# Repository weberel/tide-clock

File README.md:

# Tide Clock

A battery-powered e-paper display showing tide times. Configurable for any coastal location. This device does not need an internet or bluetooth connection as all data is calculated on the device itself from a given time and location. Thanks to the display type and slow refreshrate with long sleep cycles this device can operate on two AA-batteries for at least 3 years.

## Features

- **Tide prediction** - Next high/low tide times using a 31-constituent harmonic model
- **Moon phase** - Current phase with upcoming full/new moon dates
- **Sunrise/Sunset** - Daily times with 24-hour daylight visualization bar
- **Special messages** - Solstices, equinoxes, eclipses, meteor showers, holidays
- **Offline operation** - Pure mathematical models, no internet required
- **Multi-year battery life** - 15-minute wake cycles with deep sleep between updates

## Hardware

- **MCU**: STM32F411RET6 (ARM Cortex-M4)
- **Display**: 2.9" e-paper (296x128, SSD1680 controller)
- **RTC**: DS3231MZ+ with alarm wake
- **Power**: AA batteries with TPS61099 boost converter

## Project Structure

```
tidal-clock/
├── firmware/          # STM32 firmware (Rev A & B)
├── simulator/         # SDL2 simulator for testing
├── scripts/           # Location config generation
│   └── harmonic_fitting/  # Tide model fitting
├── kicad/             # PCB designs
└── manual/            # User manual
```

Each folder has its own README with detailed instructions.

## Quick Start

### Simulator

```bash
cd simulator
sudo apt install libsdl2-dev
git clone https://github.com/olikraus/u8g2.git
make && ./tide_sim
```

### Firmware

```bash
cd firmware/revA  # or revB
cd lib && git clone https://github.com/olikraus/u8g2.git && cd ..
pio run --target upload
```

## Customizing Location

Configure for any coastal location. See [scripts/README.md](scripts/README.md) for details.

**US locations** (using NOAA API):
```bash
cd scripts
python3 generate_location.py --noaa 9414290 --name "San Francisco" --tz US_PACIFIC
```

**Other locations** (fit your own model):
```bash
python3 generate_location.py --json harmonic_fitting/model.json --name "Location" --tz UK
```

## License

MIT

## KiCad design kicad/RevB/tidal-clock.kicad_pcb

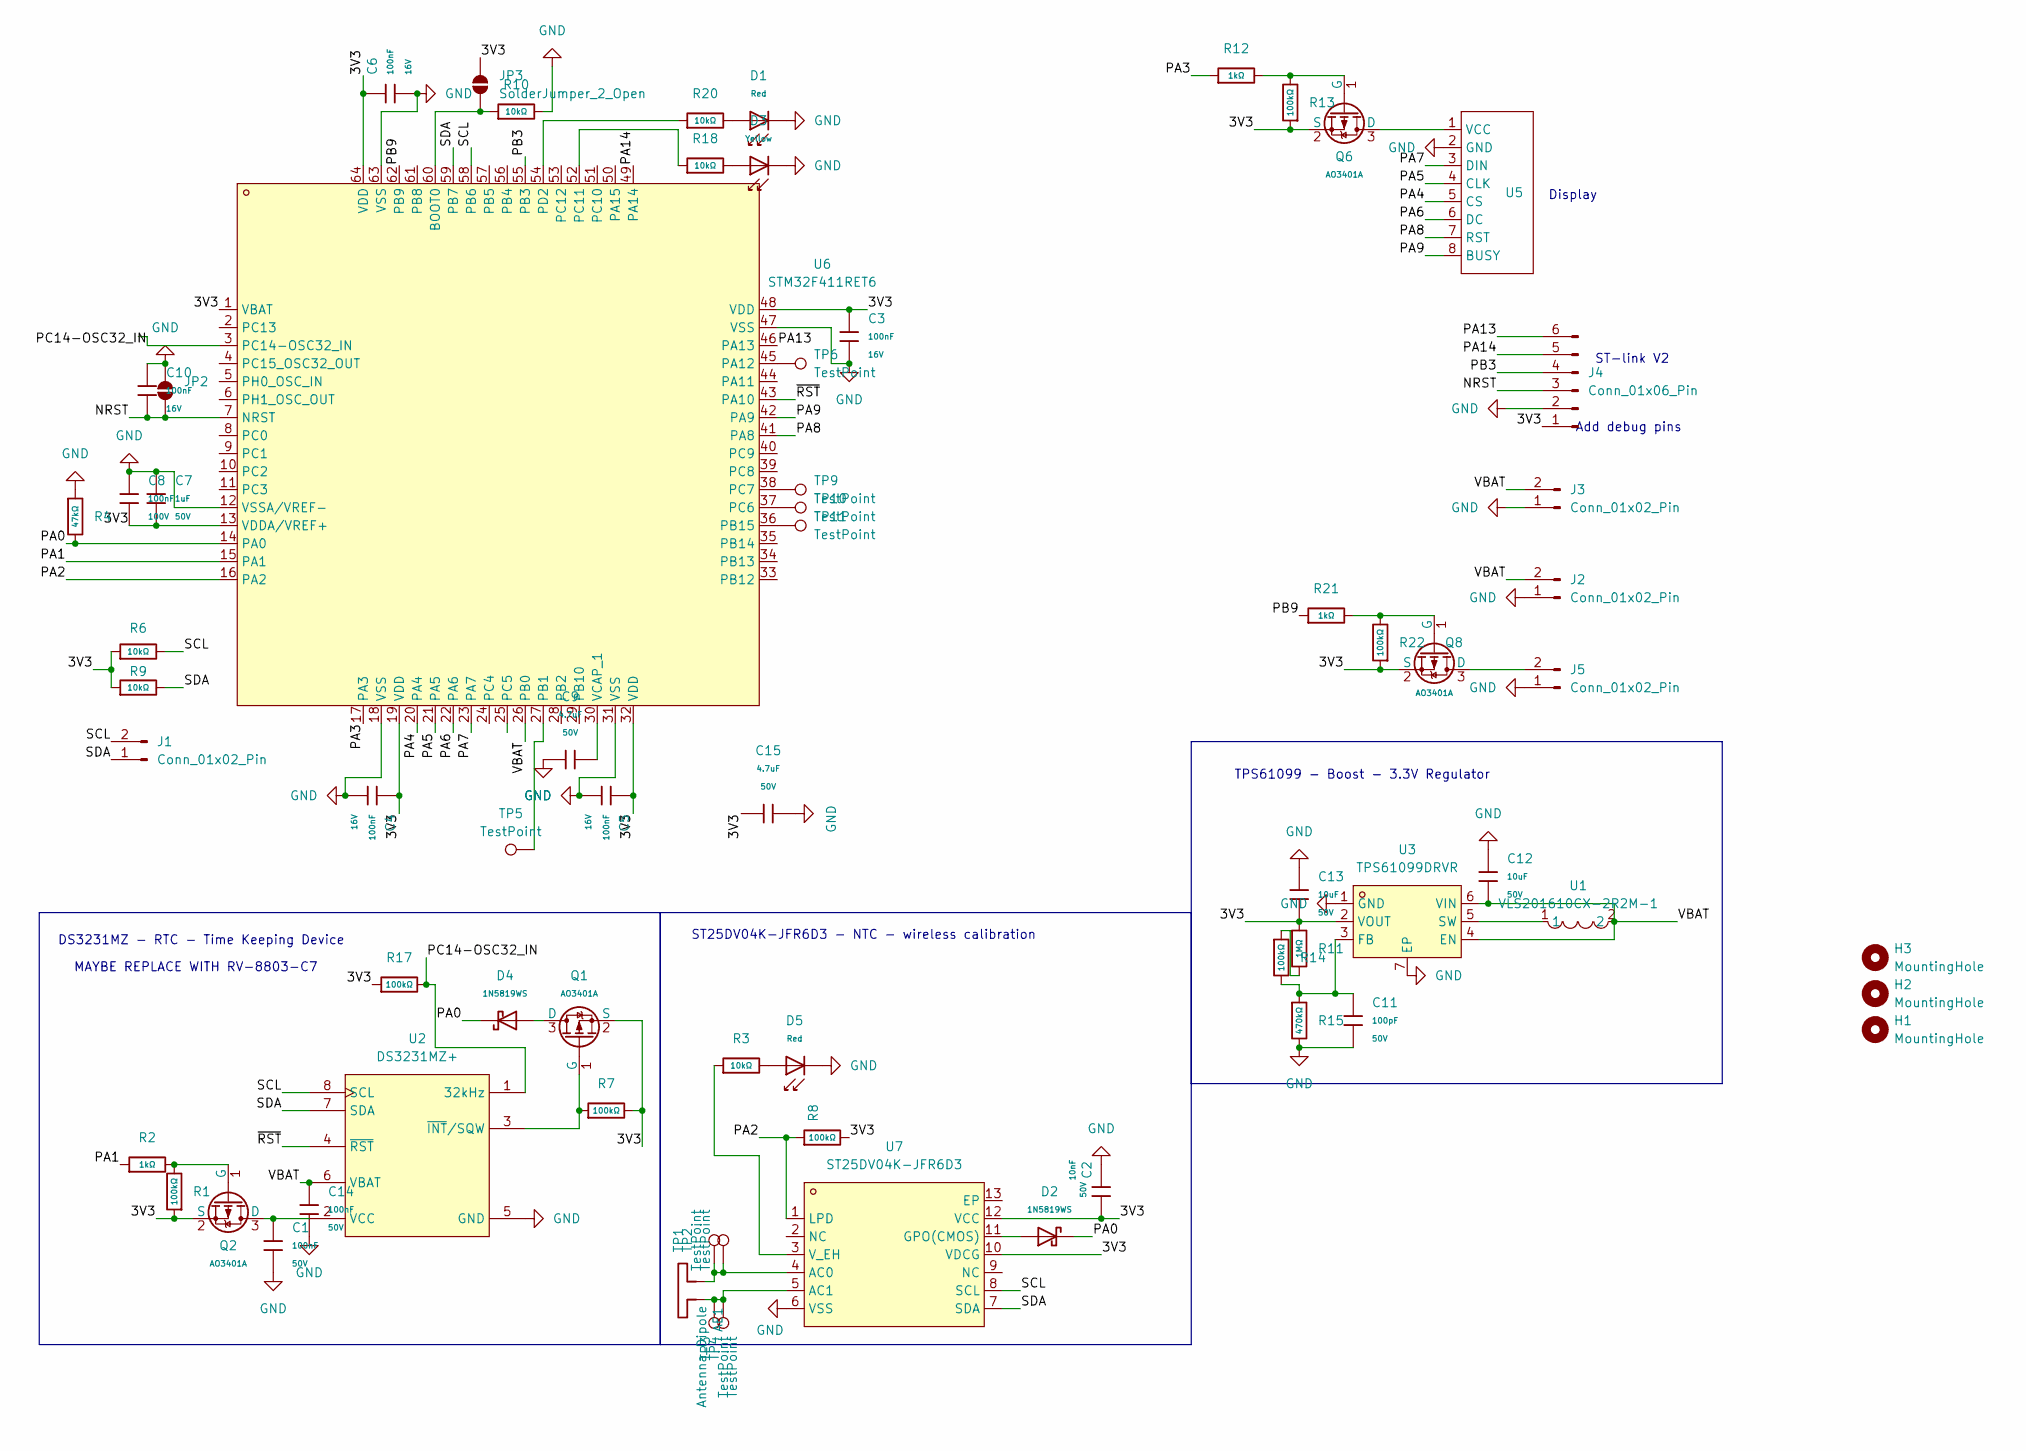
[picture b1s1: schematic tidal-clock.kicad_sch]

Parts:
AE1: Antenna_Dipole; NFC_COIL
C1, C14: 100nF; C_0603; Voltage Rated 50V; Tolerance ±10%; Part CC0603KRX7R9BB104; LCSC C14663
C2: 10nF; C_0402; Voltage Rated 50V; Tolerance ±10%; Part CL05B103KB5NNNC; LCSC C15195
C3, C4, C5, C6, C10: 100nF; C_0402; Voltage Rated 16V; Tolerance ±10%; Part CL05B104KO5NNNC; LCSC C1525
C7: 1uF; C_0805; Voltage Rated 50V; Tolerance ±10%; Part CL21B105KBFNNNE; LCSC C28323
C8: 100nF; C_0805; Voltage Rated 100V; Tolerance ±10%; Part CL21B104KCFNNNE; LCSC C28233
C9, C15: 4.7uF; C_1206; Voltage Rated 50V; Tolerance ±10%; Part 1206B475K500NT; LCSC C29823
C11: 100pF; C_0402; Voltage Rated 50V; Tolerance ±5%; Part 0402CG101J500NT; LCSC C1546
C12, C13: 10uF; C_1206; Voltage Rated 50V; Tolerance ±10%; Part CL31A106KBHNNNE; LCSC C13585
D1, D5: Red; D_0603; Part KT-0603R; LCSC C2286
D2, D4: 1N5819WS; D_SOD-323; Forward Voltage (Vf@If) 600mV@1A; Reverse Voltage (Vr) 40V; Part 1N5819WS; LCSC C191023
D3: Yellow; D_0603; Forward Voltage (VF) 1.6V~2.6V; Part NCD0603Y2; LCSC C89811
H1, H2, H3: MountingHole; MountingHole_2.2mm_M2_ISO14580
J1, J2, J3, J5: Conn_01x02_Pin; PinHeader_1x02_P2.54mm_Vertical
J4: Conn_01x06_Pin; PinSocket_1x06_P2.54mm_Vertical
JP2, JP3: SolderJumper_2_Open; SolderJumper-2_P1.3mm_Open_RoundedPad1.0x1.5mm
Q1, Q2, Q6, Q8: AO3401A; Q_SOT-23; Part AO3401A; LCSC C15127
R1, R7, R8, R13, R14, R17, R22: 100kΩ; R_0603; Overload Voltage (Max) 75V; Tolerance ±1%; Part 0603WAF1003T5E; LCSC C25803
R2, R12, R21: 1kΩ; R_0603; Overload Voltage (Max) 75V; Tolerance ±1%; Part 0603WAF1001T5E; LCSC C21190
R3, R18, R20: 10kΩ; R_0402; Overload Voltage (Max) 50V; Tolerance ±1%; Part 0402WGF1002TCE; LCSC C25744
R4: 47kΩ; R_0603; Overload Voltage (Max) 75V; Tolerance ±1%; Part 0603WAF4702T5E; LCSC C25819
R6, R9, R10: 10kΩ; R_0603; Overload Voltage (Max) 75V; Tolerance ±1%; Part 0603WAF1002T5E; LCSC C25804
R11: 1MΩ; R_0603; Overload Voltage (Max) 75V; Tolerance ±1%; Part 0603WAF1004T5E; LCSC C22935
R15: 470kΩ; R_0603; Overload Voltage (Max) 75V; Tolerance ±1%; Part 0603WAF4703T5E; LCSC C23178
TP1, TP2, TP3, TP4: TestPoint; TestPoint_Pad_1.0x1.0mm
TP5, TP6, TP9, TP10, TP11: TestPoint; TestPoint_Pad_D1.5mm
U1: VLS201610CX-2R2M-1; IND-SMD_L2.0-W1.6; LCSC Part C2041554
U2: DS3231MZ+; SOIC-8_L4.9-W3.9-P1.27-LS6.0-BL; LCSC Part C107410
U3: TPS61099DRVR; WSON-6_L2.0-W2.0-P0.65-TL-EP; LCSC Part C2842395
U5: PinHeader_1x08_P2.54mm_Vertical
U6: STM32F411RET6; LQFP-64_L10.0-W10.0-P0.50-LS12.0-BL; LCSC Part C94355
U7: ST25DV04K-JFR6D3; UDFN-12_L3.0-W3.0-P0.50-TR-EP; LCSC Part C2654815

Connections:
/3V3: C2.1, C3.1, C4.1, C5.1, C6.1, C7.2, C8.2, C13.2, C15.1, J4.1, JP3.2 (B), Q1.2 (S), Q2.2 (S), Q6.2 (S), Q8.2 (S), R1.1, R6.1, R7.2, R8.2, R9.1, R11.1, R13.1, R17.1, R22.1, U3.2 (VOUT), U6.1 (VBAT), U6.13 (VDDA/VREF+), U6.19 (VDD), U6.32 (VDD), U6.48 (VDD), U6.64 (VDD), U7.10 (VDCG), U7.12 (VCC)
/NRST: C10.2, J4.3, JP2.1 (A), U6.7 (NRST)
/PA0: D2.1, D4.1, R4.2, U6.14 (PA0)
/PA1: R2.1, U6.15 (PA1)
/PA2: R8.1, U6.16 (PA2), U7.1 (LPD)
/PA3: R12.1, U6.17 (PA3)
/PA4: U5.5 (CS), U6.20 (PA4)
/PA5: U5.4 (CLK), U6.21 (PA5)
/PA6: U5.6 (DC), U6.22 (PA6)
/PA7: U5.3 (DIN), U6.23 (PA7)
/PA8: U5.7 (RST), U6.41 (PA8)
/PA9: U5.8 (BUSY), U6.42 (PA9)
/PA13: J4.6, U6.46 (PA13)
/PA14: J4.5, U6.49 (PA14)
/PB3: J4.4, U6.55 (PB3)
/PB9: R21.1, U6.62 (PB9)
/PC14-OSC32_IN: R17.2, U2.1 (32kHz), U6.3 (PC14-OSC32_IN)
/SCL: J1.2, R6.2, U2.8 (SCL), U6.58 (PB6), U7.8 (SCL)
/SDA: J1.1, R9.2, U2.7 (SDA), U6.59 (PB7), U7.7 (SDA)
/VBAT: C12.2, C14.1, J2.2, J3.2, U1.2, U2.6 (VBAT), U3.4 (EN), U3.6 (VIN), U6.26 (PB0)
/~RST: U2.4 (~RST), U6.43 (PA10)
GND: C1.2, C2.2, C3.2, C4.2, C5.2, C6.2, C7.1, C8.1, C9.1, C10.1, C11.2, C12.1, C13.1, C14.2, C15.2, D1.1, D3.1, D5.1, J2.1, J3.1, J4.2, J5.1, JP2.2 (B), R4.1, R10.2, R15.2, U2.5 (GND), U3.1 (GND), U3.7 (EP), U5.2 (GND), U6.12 (VSSA/VREF-), U6.18 (VSS), U6.31 (VSS), U6.47 (VSS), U6.63 (VSS), U7.6 (VSS)
unnamed: D1.2, R20.2
unnamed: D3.2, R18.2
unnamed: D5.2, R3.2
unnamed: J5.2, Q8.3 (D)
unnamed: JP3.1 (A), R10.1, U6.60 (BOOT0)
unnamed: D4.2, Q1.3 (D)
unnamed: Q1.1 (G), R7.1, U2.3 (~INT/SQW)
unnamed: C1.1, Q2.3 (D), U2.2 (VCC)
unnamed: Q2.1 (G), R1.2, R2.2
unnamed: Q6.3 (D), U5.1 (VCC)
unnamed: Q6.1 (G), R12.2, R13.2
unnamed: Q8.1 (G), R21.2, R22.2
unnamed: R11.2, R14.1
unnamed: C11.1, R14.2, R15.1, U3.3 (FB)
unnamed: U1.1, U3.5 (SW)
unnamed: TP6.1, U6.45 (PA12)
unnamed: TP5.1, U6.27 (PB1)
unnamed: TP11.1, U6.36 (PB15)
unnamed: TP10.1, U6.37 (PC6)
unnamed: TP9.1, U6.38 (PC7)
unnamed: R18.1, U6.52 (PC11)
unnamed: R20.1, U6.54 (PD2)
unnamed: C9.2, U6.30 (VCAP_1)
unnamed: AE1.1, TP1.1, TP2.1, U7.4 (AC0)
unnamed: AE1.2, TP3.1, TP4.1, U7.5 (AC1)
unnamed: D2.2, U7.11 (GPO(CMOS))
unnamed: R3.1, U7.3 (V_EH)

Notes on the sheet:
Add debug pins
TPS61099 - Boost - 3.3V Regulator
ST-link V2
DS3231MZ - RTC - Time Keeping Device
MAYBE REPLACE WITH RV-8803-C7
Display
ST25DV04K-JFR6D3 - NTC - wireless calibration

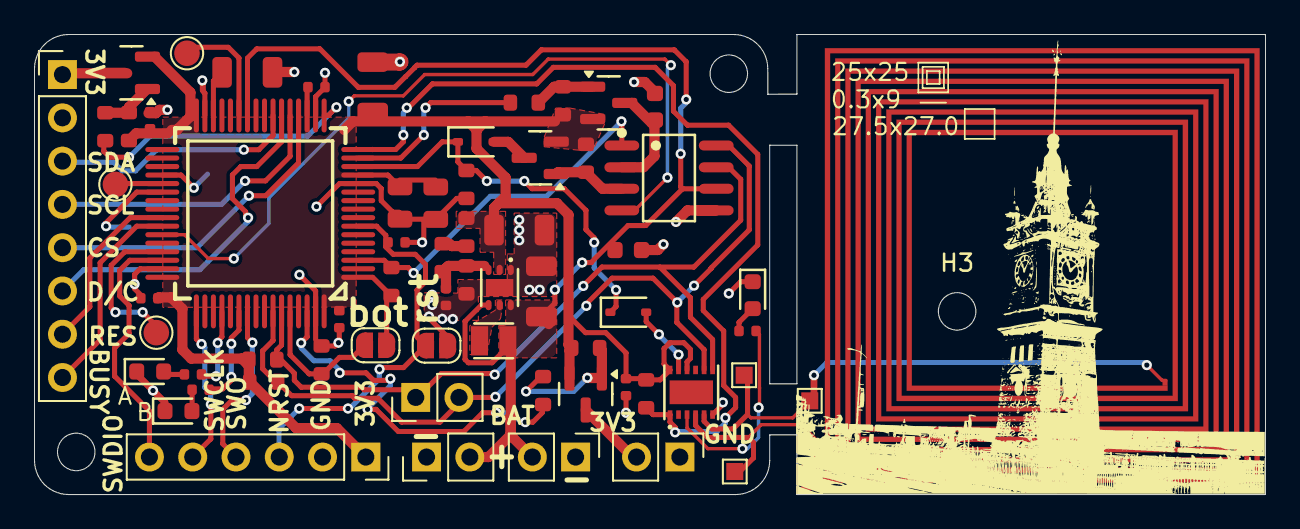
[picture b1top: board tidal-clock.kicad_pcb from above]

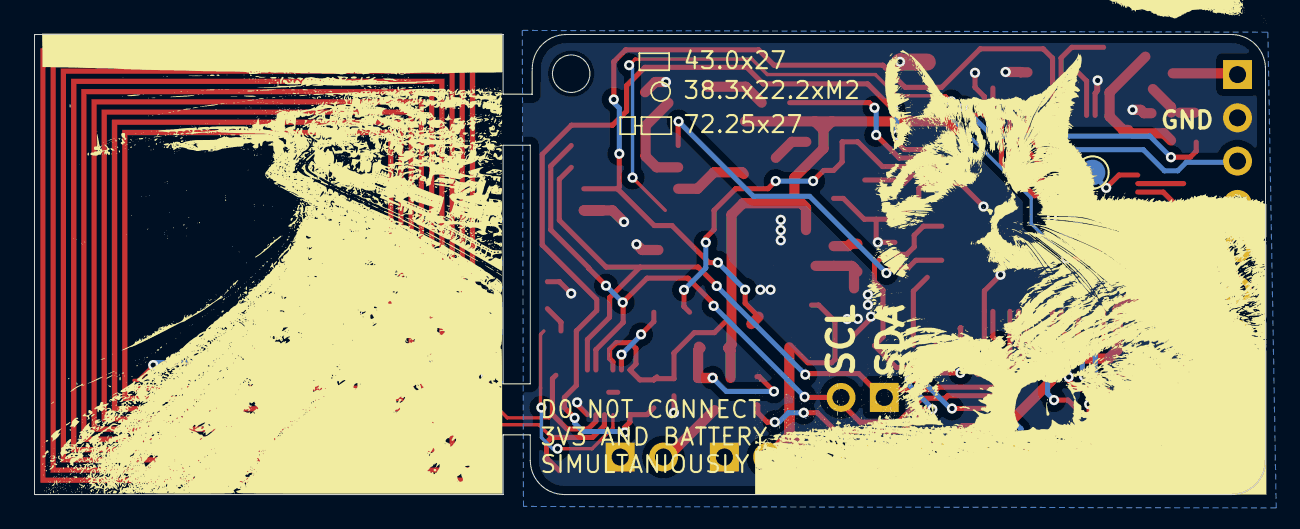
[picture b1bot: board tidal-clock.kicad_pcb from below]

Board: 2 copper layers, 72.2 x 27.0 mm, 69 parts (2 on the bottom side), 49 nets.

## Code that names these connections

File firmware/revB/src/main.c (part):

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 *
 * Hardware changes from Rev A:
 * - ST25DV04K NFC instead of NT3H2111
 * - PA2 now NFC LPD (Low Power Down) instead of power gate
 * - PA0 wakeup via OR diode: DS3231 alarm (via MOSFET) OR ST25DV GPO (direct)
 * - PB9 external 3V3 power gate
 * - Removed parasitic pullup on DS3231 RST
 * - Button removed (time set via NFC)
 *
 * Wake cycle:
 * 1. Wake from STOP mode (PA0 rising edge from RTC alarm OR NFC field)
 * 2. Determine wake source (RTC alarm vs NFC field)
 * 3. If NFC: check for time sync data, update RTC if valid
 * 4. If RTC alarm: normal display update cycle
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#define LED2_PIN    GPIO_PIN_11
#define LED2_PORT   GPIOC

// Wakeup (PA0) - OR'd signal from:
// - DS3231 INT (active low) -> P-FET inverter -> HIGH when alarm
// - ST25DV GPO (CMOS) -> HIGH when RF field detected
// Both go through OR diodes to PA0 (pulled low)
#define WAKEUP_PIN  GPIO_PIN_0   // PA0 - Combined wakeup signal
#define WAKEUP_PORT GPIOA

// Power gates (active LOW - P-FET)
#define RTC_PWR     GPIO_PIN_1   // PA1 - DS3231 VCC gate
#define NFC_LPD     GPIO_PIN_2   // PA2 - ST25DV LPD (HIGH=sleep, LOW=active)
#define EPD_PWR     GPIO_PIN_3   // PA3 - Display VCC gate
#define EXT_PWR     GPIO_PIN_9   // PB9 - External 3V3 output gate (active LOW)
#define EXT_PWR_PORT GPIOB

// Battery and debug
#define VBAT_PIN    GPIO_PIN_0   // PB0 - Battery voltage (ADC1_IN8)
#define VBAT_PORT   GPIOB

// ST-Link debug pin exposed on Rev B
#define DEBUG_PIN   GPIO_PIN_3   // PB3 - SWO (optional debug output)

// Battery thresholds (2x AA in series)
// ADC reads 0-4095 for 0-3.3V (assuming direct connection, no divider)
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    g.Pin = LED2_PIN;
    HAL_GPIO_Init(LED2_PORT, &g);

    // Button (PB1) - input with internal pull-up
    g.Pin = BTN_PIN;
    g.Mode = GPIO_MODE_INPUT;
    g.Pull = GPIO_PULLUP;
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    __HAL_RCC_GPIOB_CLK_ENABLE();

    GPIO_InitTypeDef g = {0};
    g.Pin = GPIO_PIN_6 | GPIO_PIN_7;  // PB6 = SCL, PB7 = SDA
    g.Mode = GPIO_MODE_AF_OD;
    g.Pull = GPIO_PULLUP;
    g.Speed = GPIO_SPEED_FREQ_HIGH;
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    __HAL_RCC_ADC1_CLK_ENABLE();
    __HAL_RCC_GPIOB_CLK_ENABLE();

    // Configure PB0 as analog input
    GPIO_InitTypeDef g = {0};
    g.Pin = VBAT_PIN;
    g.Mode = GPIO_MODE_ANALOG;
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    hadc.Init.EOCSelection = ADC_EOC_SINGLE_CONV;
    HAL_ADC_Init(&hadc);

    // Configure channel 8 (PB0)
    ADC_ChannelConfTypeDef ch = {0};
    ch.Channel = ADC_CHANNEL_8;
    ch.Rank = 1;
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}

/**
 * Enter STOP mode while waiting for display BUSY pin (PA9) to go LOW.
 * Display power must remain ON during this time.
 * EXTI9 falling edge wakes the MCU when display is ready.
 */
void enter_stop_mode_wait_display(void) {
    // Configure PA9 (BUSY) as input
    GPIO_InitTypeDef gpio = {0};
    gpio.Pin = GPIO_PIN_9;
    gpio.Mode = GPIO_MODE_INPUT;
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/**
 * Set all GPIOs to analog mode for lowest power consumption.
 * In analog mode, the input Schmitt trigger is disabled, preventing leakage.
 * Only exception: PA0 (WKUP pin) needs to stay functional.
 */
void GPIO_DeInit_For_Standby(void) {
    GPIO_InitTypeDef gpio = {0};
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    gpio.Pull = GPIO_NOPULL;
    gpio.Speed = GPIO_SPEED_FREQ_LOW;

    // De-init I2C peripheral first (releases PB6/PB7)
    HAL_I2C_DeInit(&hi2c);
    __HAL_RCC_I2C1_CLK_DISABLE();

    // De-init SPI peripheral (releases PA5/PA7)
    __HAL_RCC_SPI1_CLK_DISABLE();

    // === DISABLE LSE OSCILLATOR ===
    // PC14/PC15 are controlled by backup domain, not normal GPIO
    // The LSE amplifier draws ~50µA if enabled with external signal
    __HAL_RCC_PWR_CLK_ENABLE();
    HAL_PWR_EnableBkUpAccess();  // Unlock backup domain
    __HAL_RCC_LSE_CONFIG(RCC_LSE_OFF);  // Disable LSE oscillator
    HAL_PWR_DisableBkUpAccess();  // Lock backup domain

    // GPIOA: Set all pins to analog EXCEPT PA0 (WKUP pin)
    // PA0 = WKUP (keep as is - hardware handles it)
    // PA1-PA15 = analog
    gpio.Pin = GPIO_PIN_1 | GPIO_PIN_2 | GPIO_PIN_3 | GPIO_PIN_4 |
               GPIO_PIN_5 | GPIO_PIN_6 | GPIO_PIN_7 | GPIO_PIN_8 |
               GPIO_PIN_9 | GPIO_PIN_10 | GPIO_PIN_11 | GPIO_PIN_12 |
               GPIO_PIN_13 | GPIO_PIN_14 | GPIO_PIN_15;
    HAL_GPIO_Init(GPIOA, &gpio);

    // GPIOB: All pins to analog (including I2C PB6/PB7)
    gpio.Pin = GPIO_PIN_All;
    HAL_GPIO_Init(GPIOB, &gpio);

    // GPIOC: All pins to analog (PC14/PC15 now safe after LSE disabled)
    HAL_GPIO_Init(GPIOC, &gpio);

    // GPIOD: All pins to analog
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}

/**
 * Enter STANDBY mode. MCU will wake on WKUP pin (PA0 rising edge).
 * This is the lowest power mode - 1.2V domain is powered off.
 * On wake-up, MCU performs a full reset (like power-on).
 */
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    // Clear wake-up flag (must be cleared before entering standby)
    __HAL_PWR_CLEAR_FLAG(PWR_FLAG_WU);

    // Enable WKUP pin (PA0) - rising edge will wake from standby
    HAL_PWR_EnableWakeUpPin(PWR_WAKEUP_PIN1);

    // Enter STANDBY mode
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    // Display is now done - power it off (it will retain image)
    HAL_GPIO_WritePin(GPIOA, EPD_PWR, GPIO_PIN_SET);

    // Enter STANDBY mode - MCU will reset on wake-up (PA0 rising edge from DS3231)
    // This function does not return - main() runs again on wake
    enter_standby_mode();

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
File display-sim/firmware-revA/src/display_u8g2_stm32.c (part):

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 * Uses IL3820/SSD1680 driver for 2.9" e-paper display (128x296).
 *
 * Pin mapping (from pinout.txt):
 *   PA3: Display VCC gate (P-FET, LOW=ON)
 *   PA4: CS
 *   PA5: CLK (SPI1_SCK)
 *   PA6: DC
 *   PA7: DIN (SPI1_MOSI)
 *   PA8: RST
 *   PA9: BUSY
 */

#include "display.h"
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    __HAL_RCC_SPI1_CLK_ENABLE();
    __HAL_RCC_GPIOA_CLK_ENABLE();

    // Configure SPI pins: CLK (PA5), MOSI (PA7)
    GPIO_InitTypeDef gpio = {0};
    gpio.Pin = EPD_CLK_PIN | EPD_DIN_PIN;
    gpio.Mode = GPIO_MODE_AF_PP;
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
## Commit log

2026-01-06 Initial commit - Tidal Clock for Margate, UK
    Low-power e-paper display showing tide times, moon phases, and astronomical
    information. Designed for multi-year battery life with 15-minute update cycles.
    Features:
    - 31-constituent harmonic tide model (~5 min accuracy)
    - Moon phase with Meeus algorithm
    - Sunrise/sunset with NOAA algorithm
2026-01-06 updates pics
2026-01-07 changed folder structure
2026-01-07 split big file
2026-01-07 Added location suppoer including NOAA API
2026-01-07 fixes.. NOAA data not perfect.
2026-01-07 licence
